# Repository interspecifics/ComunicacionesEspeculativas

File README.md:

# ComunicacionesEspeculativas
Es un proyecto basado en una máquina que es capaz de observar y aprender de
microorganismos para crear un score audiovisual a partir de los patrones que encuentre en su comportamiento. Este proyecto se apoya en la creación de una inteligencia artificial, la cual reconoce comportamientos organizados reiterativos en cultivos biológicos y los transforma en eventos que dota de una gestualidad audiovisual específica con el fin de lograr una composición autogenerativa que responde a las lógicas de decisión que esta inteligencia construye con el tiempo. 

## Instalación CV2.4.9 en Mac
1 - Instalar brew http://brew.sh/

>brew tap homebrew/science

>brew install opencv

## Instalación CV2 en la raspberry

seguir el tutorial que se encuentra aquí:
https://www.pyimagesearch.com/2015/02/23/install-opencv-and-python-on-your-raspberry-pi-2-and-b/

## Instalación netatalk

1- Installation:

>sudo apt-get update

>sudo apt-get install netatalk

2- Configuration

**Stop the service:**

>sudo /etc/init.d/netatalk stop

**Open the configuration file:**

>sudo nano /etc/netatalk/AppleVolumes.default

**You can edit the mount folder if you wish or leave the default value:**

>~/ "Home Directory"

**Start the service again**

>sudo /etc/init.d/netatalk start

## Configurar USB como storage local

**1 - To mount a USB drive:**

>sudo mkdir /mnt/usbdrive

>sudo mount /dev/sda1 /mnt/usbdrive

>ls /mnt/usbdrive

**2 - To list your file systems:**

>sudo fdisk -l

>sudo mount -l

>df -h

**3- Before disconnecting a USB drive:**

>sudo umount /dev/sda1

**4- Format a drive to EXT4**

>sudo mkfs.ext4 /dev/sda1 -L untitled

**5- Create a mount point**

>sudo mkdir /mnt/usbdrive

**6- Check the dev directory

>/dev/sd*

**7- To mount the drive to your mount point ‘usbdrive‘.

>sudo mount /dev/sda1 /mnt/usbdrive

**8- Disconnect / Unmount A Drive**

>sudo umount /dev/sda1

## Biotracker XY

Para la construcción de biotracker xy es necesario la impresión de la piezas que se encuentran aquí :

https://github.com/interspecifics/ComunicacionesEspeculativas/tree/master/Impresion%203d%20XY

## Controllers 

Actualmente existe dos placas electrónicas para el control de los dos dispositivos disponibles el Microscopio Z y el Biotracker X/Y

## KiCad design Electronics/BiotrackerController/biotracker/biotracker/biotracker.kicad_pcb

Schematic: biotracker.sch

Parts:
J1: USB_B_Micro; USB_Micro-B_Amphenol_10103594-0001LF_Horizontal
J2: Jack-DC; BarrelJack_Horizontal
J3: Conn_01x03_Male; PinHeader_1x03_P2.54mm_Vertical
M1: MiniStepper_X; PinHeader_1x04_P2.54mm_Vertical
M2: MiniStepper_Y; PinHeader_1x04_P2.54mm_Vertical
M3: Stepper_Z; PinHeader_1x04_P2.54mm_Vertical
R1, R2: 10K; R_Axial_DIN0207_L6.3mm_D2.5mm_P10.16mm_Horizontal
RV1: 10K; Potentiometer_Alps_RK163_Single_Horizontal
SW1: SWPush_A; SW_PUSH-12mm
SW2: SWPush_B; SW_PUSH-12mm
U1: Teensy3.2; Teensy30_31_32_LC
U2: ADA_Joystick; ADA_joystick
U3, U4: DRV8833; ADA_DRV8833
U5: TB6612; ADA_TB6612

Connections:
3V_bus: R1.1, R2.1, RV1.1, U1.31, U3.6, U4.6, U5.4, U5.7, U5.10
5V_bus: J1.1, U1.33, U2.1, U3.1, U4.1
12V_bus: J2.1, U5.1
GND: J1.5, J1.6, J2.2, J3.3, RV1.3, SW1.1, SW2.1, U1.1, U2.5, U3.2, U4.2, U5.3
Joy_X: U1.23, U2.2
Joy_Y: U1.24, U2.3
LED1: J3.2, U1.4
LED2: J3.1, U1.5
MotX_AIn1: U1.11, U3.8
MotX_AIn2: U1.10, U3.7
MotX_BIn1: U1.12, U3.4
MotX_BIn2: U1.13, U3.5
MotY_AIn1: U1.7, U4.8
MotY_AIn2: U1.6, U4.7
MotY_BIn1: U1.8, U4.4
MotY_BIn2: U1.9, U4.5
MotZ_AIn1: U1.29, U5.8
MotZ_AIn2: U1.30, U5.9
MotZ_BIn1: U1.28, U5.6
MotZ_BIn2: U1.27, U5.5
unnamed: M1.1, U3.11
unnamed: M1.2, U3.12
unnamed: M1.3, U3.10
unnamed: M1.4, U3.9
unnamed: M2.1, U4.11
unnamed: M2.2, U4.12
unnamed: M2.3, U4.10
unnamed: M2.4, U4.9
unnamed: M3.1, U5.15
unnamed: M3.2, U5.16
unnamed: M3.3, U5.12
unnamed: M3.4, U5.11
unnamed: RV1.2, U1.21
Push_A: R1.2, SW1.2, U1.25
Push_B: R2.2, SW2.2, U1.26

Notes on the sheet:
Negro Verde Azul Rojo
Rojo Café Negro Blanco
3Axis BioTracker by [ I N T E R S P E C I F I C S ]
2018.12
[e] 1.0

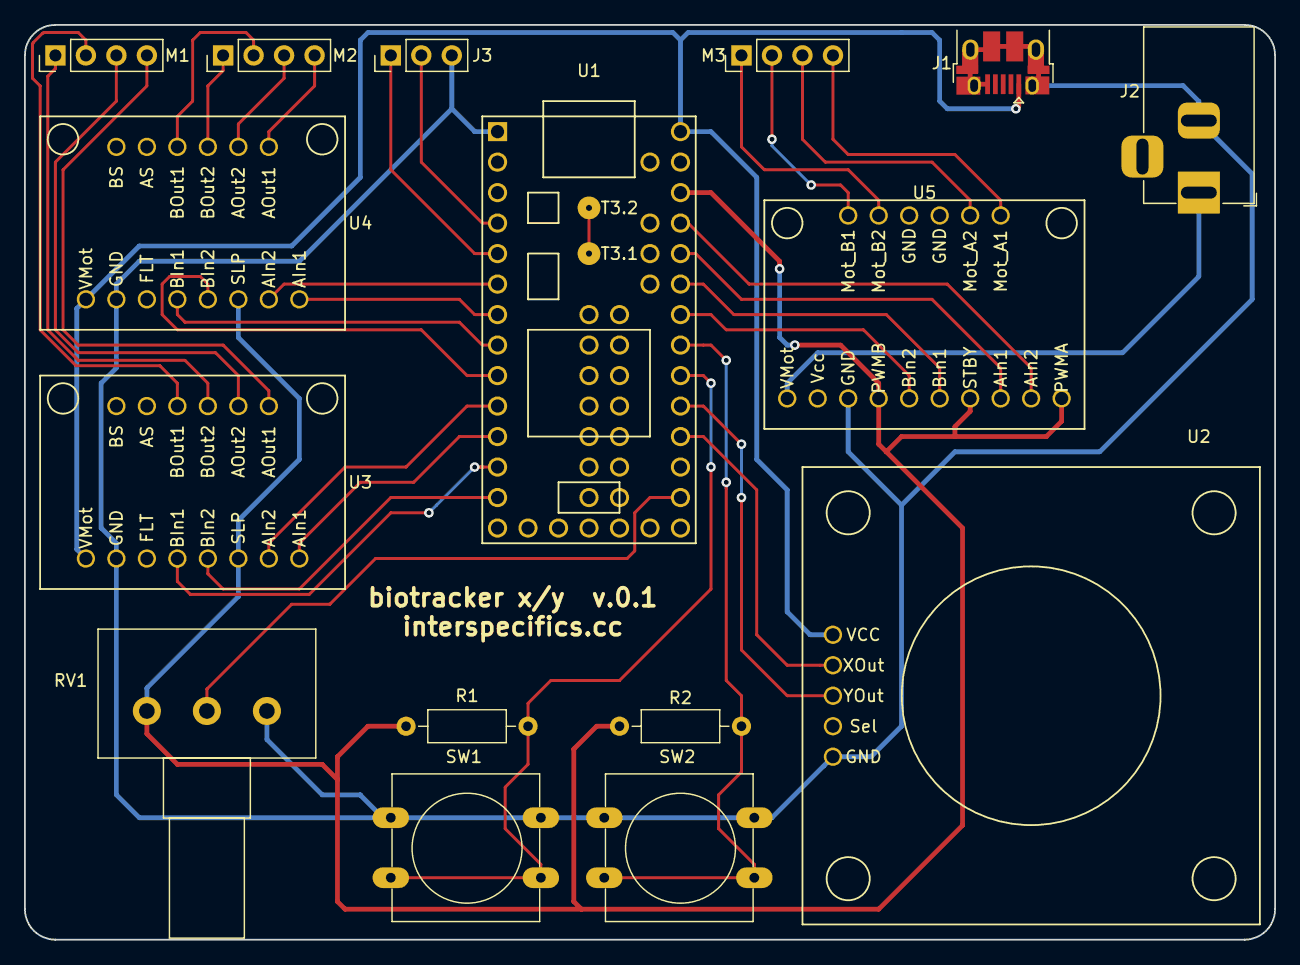
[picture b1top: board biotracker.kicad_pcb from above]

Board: 2 copper layers, 104.1 x 76.2 mm, 16 parts (0 on the bottom side), 35 nets.

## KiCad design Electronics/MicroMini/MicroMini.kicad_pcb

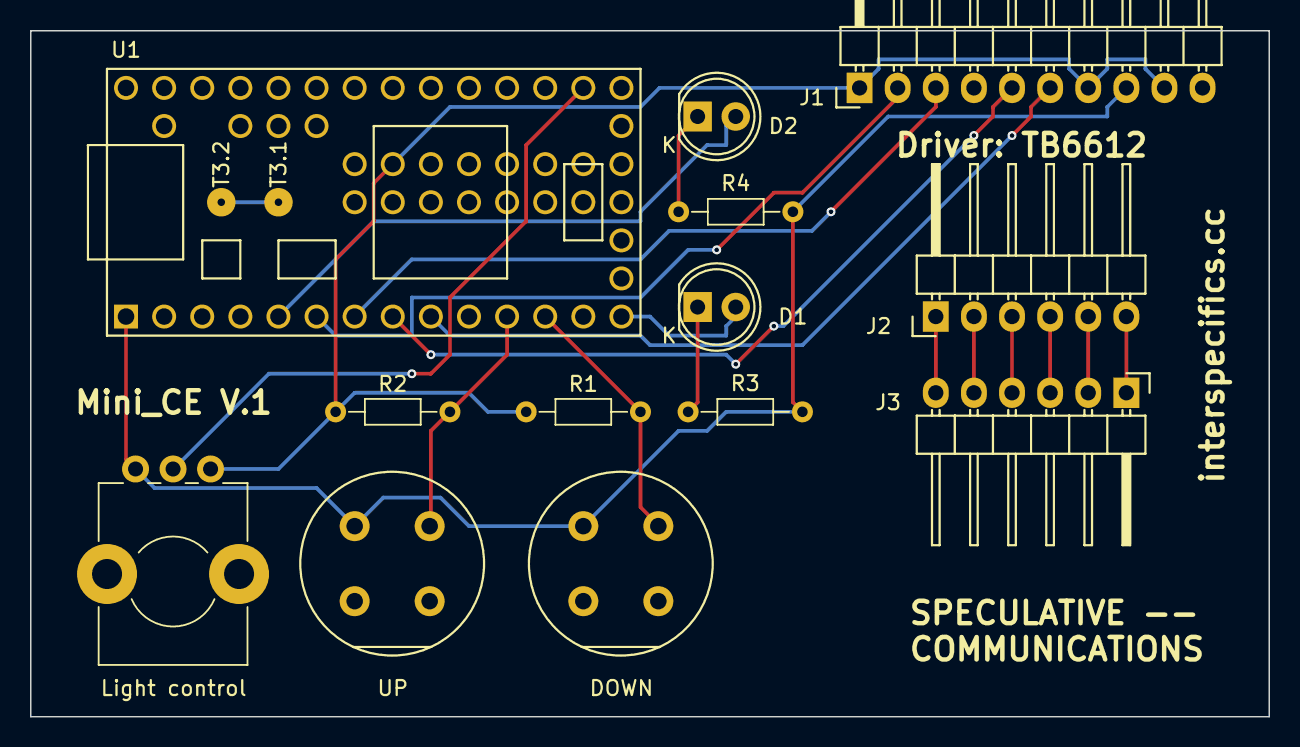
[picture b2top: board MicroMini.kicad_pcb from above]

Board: 2 copper layers, 82.6 x 45.7 mm, 13 parts (0 on the bottom side), 19 nets.

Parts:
D1, D2: LED; LED-5MM
DOWN: SW_Push; Push_E-Switch_KS01Q01
J1: Conn_01x10; Pin_Header_Angled_1x10
J2, J3: Conn_01x06; Pin_Header_Angled_1x06
Light control: POT; Potentiometer_Alps_RK09K_Horizontal
R1, R2: 10k; R_Axial_DIN0204_L3.6mm_D1.6mm_P7.62mm_Horizontal
R3, R4: R; R_Axial_DIN0204_L3.6mm_D1.6mm_P7.62mm_Horizontal
U1: Teensy3.2; Teensy30_31_32_LC
UP: SW_Push; Push_E-Switch_KS01Q01

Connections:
GND: DOWN.1, J1.8, Light control.1, R3.1, R4.1, U1.1, UP.1
unnamed: D1.1, R3.2
unnamed: D1.2, U1.14
unnamed: D2.1, R4.2
unnamed: D2.2, U1.5
unnamed: J1.1, J1.7, J1.9, Light control.3, R1.1, R2.1, U1.50
unnamed: J1.2, U1.6
unnamed: J1.3, U1.7
unnamed: J1.5, U1.8
unnamed: J1.6, U1.9
unnamed: J2.1, J3.6
unnamed: J2.2, J3.5
unnamed: J2.3, J3.4
unnamed: J2.4, J3.3
unnamed: J2.5, J3.2
unnamed: J2.6, J3.1
unnamed: DOWN.2, R1.2, U1.12
unnamed: R2.2, U1.11, UP.2
unnamed: Light control.2, U1.21

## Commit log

2017-06-13 cv2 importar video
2017-06-14 Play video
2017-06-14 load camera
2017-06-14 save video
2017-06-15 import sys
2017-06-15 color palette control
2017-06-17 opencv picamera
2017-07-19 optic flow
    tools
2017-07-21 utils
    v0.6
2017-07-21 v0.6
    0.6+
2017-07-21 006
    v06u
2017-07-21 okokok
2017-07-21 okokokok
2017-07-22 how to ce_ff_07.py
2017-07-22 visuals
    sketcj para OFX
2017-07-25 controlador de stage z
2017-07-25 change camera input
2017-07-25 number of steps per click
2017-07-25 led control
2017-07-27 comments
2017-09-06 openscad and STL files for LED and corner cube
2017-10-08 camara / videos
2018-01-09 Supercollider choose synth
    OCS message change synth still beta
2018-02-25 optics folder
2018-05-02 general control code for xyz
2018-05-02 cuadrant control for xy
2018-05-02 state of joystick
2018-05-27 circuit for controll z and code xy
2018-10-05 set speed
2018-11-20 Data Sevices
    data server added
2018-12-20 CE_sound+light
    Update con el software de las luces reactivas
2019-01-10 files for the XY version complete
2019-01-10 biotracker xy full controller
2019-01-20 added original openscad file for optics
2019-01-20 deleted replicated files
2019-07-25 new adapter for RPI cam
2019-07-27 new adapter for c270 webcam and adapter for doublet lens
